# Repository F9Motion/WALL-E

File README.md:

# WALL-E
A cube form robot. You see this robot in popular cartoon from Pixart "WALL-E".

# Why I made this
I like this cartoon since I was a kid. I try before to do this witch cardboards. But it didn't have functions to do. And time to do this robot with **Hack Club**
# Features
* Minimalistic design
* Persone from cartoon
* You like this
* Wireless
* You can control robot with controller
# How it works
When you push buttons in remote controller a special diode gives to **ESP32** signal and ESP32 gives command to motors "move!". ESP32 contacted with motors in PCB. To teach ESP32 what command give to motors I write **firmware**.
# How to assemble
1. Order PCB and parts for project(You can find parts in BOM)
2. Solder parts to PCB
3. Print all **CAD** files
4. Flash ESP32
5. Assemble it
# How to flash
1. Download arduino IDE
2. Add add-one for ESP32
3. Open my firmware
4. click to here to flash!

# Bill Of Materials

|Name         |Price |Link                     |
|-------------|------|-------------------------|
|Motors x2    |$21.76|https://ali.click/y9urq1u|
|ESP32        |$5.44 |https://ali.click/0iurq1f|
|Button       |$0.38 |https://ali.click/imurq1y|
|TYPE-C       |$1.02 |https://ali.click/irurq1j|
|Printing PCB |$10.6 |JLCPCB                   |
|eyes.step    |$6.17 |felament price only      |
|fingers.step |$0.43 |felament price only      |
|front.step   |$4.53 |felament price only      |
|hand.step    |$1.18 |felament price only      |
|platform.step|$1.91 |felament price only      |
|WALL-E step  |$14.09|felament price only      |
|sheels.step  |$3.11 |felament price only      |
|TOTAL        |$70.62|                         |

# Credits
CAD: Blender
PCB: KiCad
Who create WALL-E: Pixart
Who made it: Rasul

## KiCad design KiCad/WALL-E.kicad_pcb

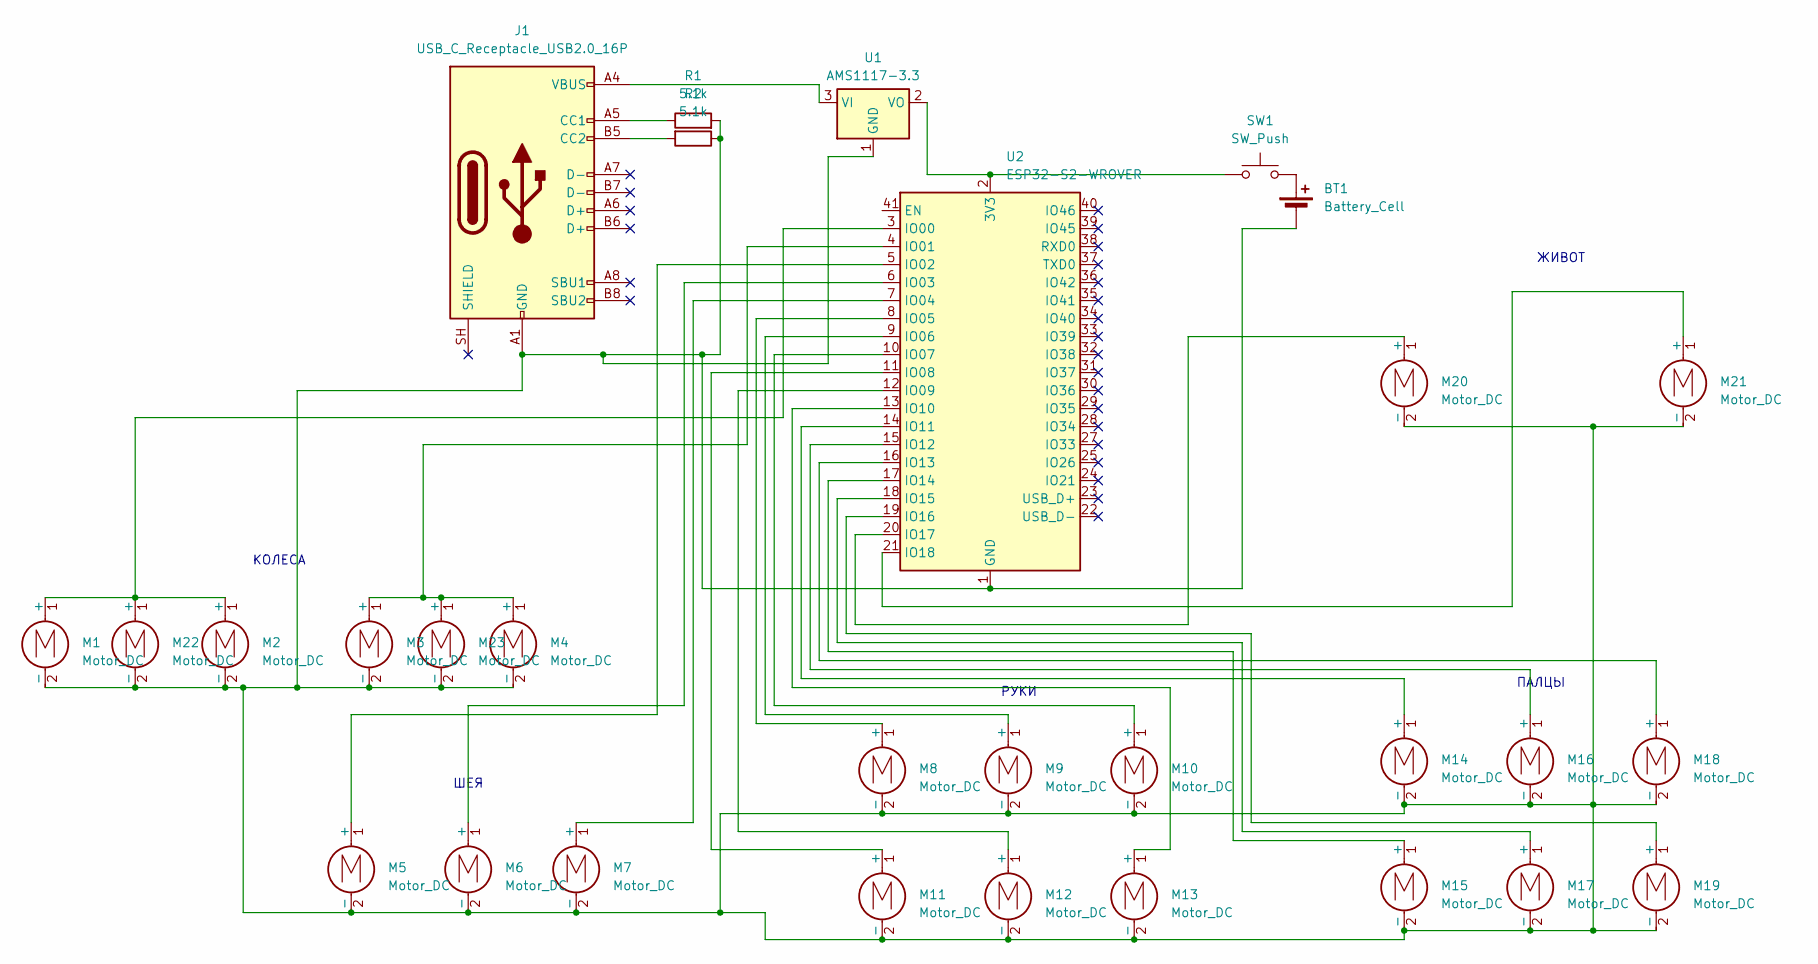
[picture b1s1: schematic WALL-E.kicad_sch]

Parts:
BT1: Battery_Cell; TerminalBlock_MaiXu_MX126-5.0-02P_1x02_P5.00mm
J1: USB_C_Receptacle_USB2.0_16P; USB_C_Receptacle_Amphenol_124019772112A
M1, M2, M3, M4, M5, M6, M7, M8, M9, M10, M11, M12, M13, M14, M15, M16, M17, M18, M19, M20, M21, M22, M23: Motor_DC; TerminalBlock_CUI_TB007-508-02_1x02_P5.08mm_Horizontal
R1, R2: 5.1k; R_0805_2012Metric
SW1: SW_Push; SW_XKB_DM1-16UC-1
U1: AMS1117-3.3; SOT-223-3_TabPin2
U2: ESP32-S2-WROVER

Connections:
unnamed: BT1.1 (+), SW1.2
unnamed: J1.A5 (CC1), R1.1
unnamed: J1.B5 (CC2), R2.2
unnamed: M1.1 (+), M2.1 (+), M22.1 (+), U2.3 (IO00)
unnamed: M5.1 (+), U2.5 (IO02)
unnamed: M6.1 (+), U2.6 (IO03)
unnamed: M7.1 (+), U2.7 (IO04)
unnamed: M8.1 (+), U2.8 (IO05)
unnamed: M9.1 (+), U2.9 (IO06)
unnamed: M10.1 (+), U2.10 (IO07)
unnamed: M11.1 (+), U2.11 (IO08)
unnamed: M12.1 (+), U2.12 (IO09)
unnamed: M13.1 (+), U2.13 (IO10)
unnamed: M14.1 (+), U2.14 (IO11)
unnamed: M15.1 (+), U2.17 (IO14)
unnamed: M16.1 (+), U2.15 (IO12)
unnamed: M17.1 (+), U2.18 (IO15)
unnamed: M18.1 (+), U2.16 (IO13)
unnamed: M19.1 (+), U2.19 (IO16)
unnamed: M20.1 (+), U2.20 (IO17)
unnamed: M21.1 (+), U2.21 (IO18)
unnamed: M3.1 (+), M4.1 (+), M23.1 (+), U2.4 (IO01)
unnamed: J1.A4 (VBUS), J1.A9 (VBUS), J1.B4 (VBUS), J1.B9 (VBUS), U1.3 (VI)
unnamed: SW1.1, U1.2 (VO), U2.2 (3V3)

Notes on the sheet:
РУКИ
ШЕЯ
ЖИВОТ
КОЛЕСА
ПАЛЦЫ

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
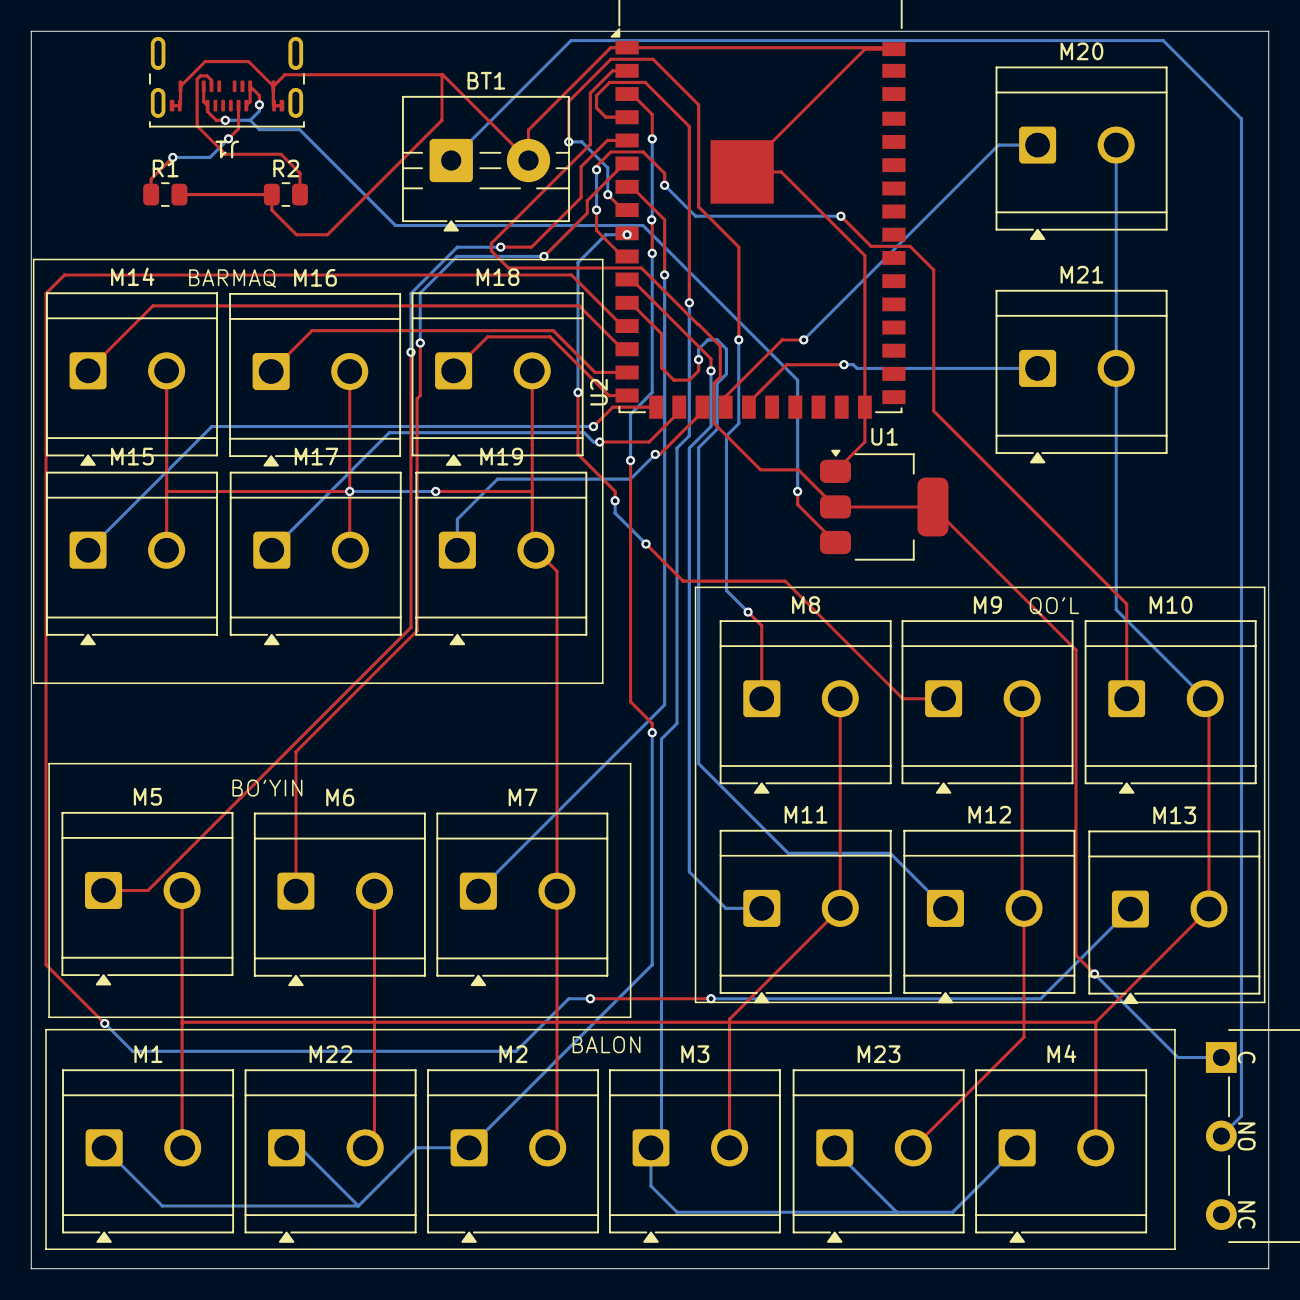
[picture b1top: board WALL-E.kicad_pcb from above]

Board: 2 copper layers, 80.0 x 80.0 mm, 30 parts (0 on the bottom side), 26 nets.
